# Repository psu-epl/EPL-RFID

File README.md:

# EPL-RFID
RFID system for controlling access to EPL machines

This repo started as copies of two separate Capstone projects in 2018: the CS
backend Capstone called LUCCA (Lab Usage Controller for Centralized Administration)
and the ECE Capstone called EPL RFID Capstone Project.

Here are links to the previous repos:

### LUCCA:
#### Repo: https://github.com/LUCCA-Capstone/LUCCA
#### Wiki: https://github.com/LUCCA-Capstone/LUCCA/wiki

### EPL RFID:
#### Repo: https://github.com/Crimson89/RFID-Capstone
#### Wiki: https://github.com/Crimson89/RFID-Capstone/wiki

# Building ESP-IDF toolchain and environment
From a linux console type the following commands:   

git clone https://github.com/psu-epl/EPL-RFID.git  
cd EPL-RFID  
git submodule update --init  

Then follow "the Setting Up ESP-IDF" directions here: https://github.com/espressif/esp-idf  

This involves lots of building packages from source. You likely don't want to do this very many times.

make sure you edit your PATH variable in your ~/.bashrc to something similar to:

export IDF_PATH=~/path/to/submodule/esp-idf  
export PATH=$PATH:/home/chad/path/to/binaries/xtensa-esp32-elf/bin:/home/chad/path/to/binaries/crosstool-NG/builds/xtensa-esp32-elf/bin/

Bad things happen when you are following the wrong path...

Focus your chi using "echo $PATH"

Code to victory brave warrior!

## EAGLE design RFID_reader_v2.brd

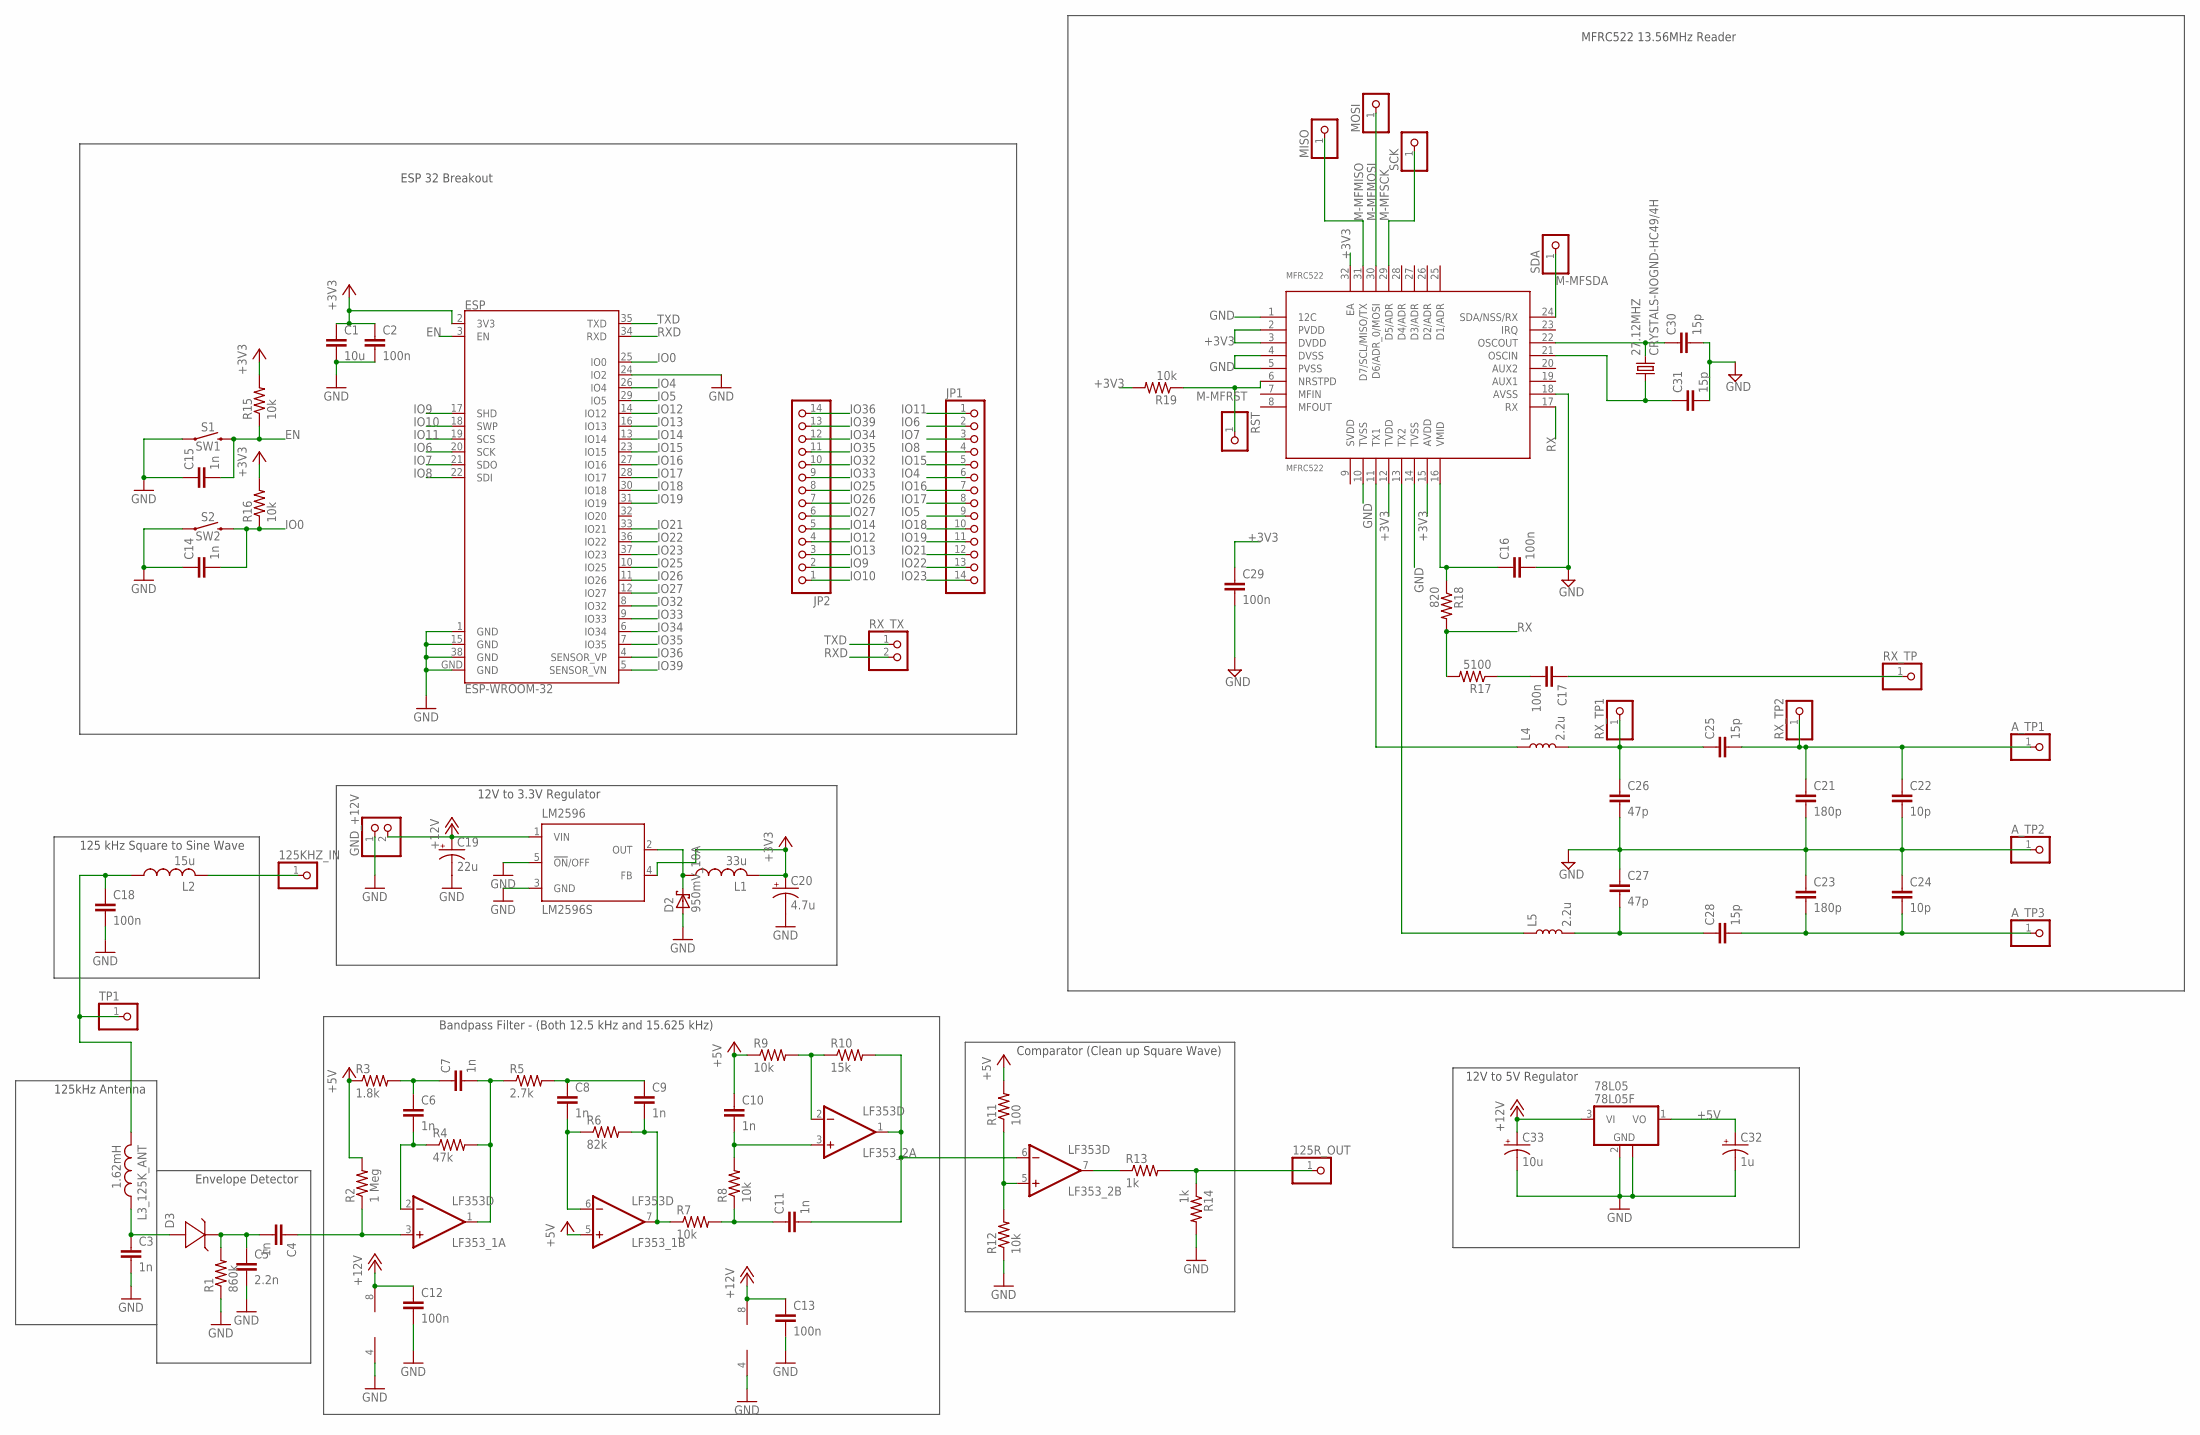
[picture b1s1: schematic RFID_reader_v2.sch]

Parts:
27.12MHZ: CRYSTALS-NOGND-HC49/4H; HC49
78L05: 78L05F; SOT89
125KHZ_IN, 125R_OUT: PINHD-1X1; 1X01
A_TP1, A_TP2, A_TP3: PINHD-1X1; 1X01
C1: 10u; C0805
C2, C12, C13, C18: 100n; C0805
C3, C4, C6, C7, C8, C9, C10, C11, C14, C15: 1n; C0805
C5: 2.2n; C0805
C16, C17, C29: 100n; C0603
C19: 22u; SANYO-OSCON_SMD_B6
C20: 4.7u; SMC_C
C21, C23: 180p; C0603
C22, C24: 10p; C0603
C25, C28, C30, C31: 15p; C0603
C26, C27: 47p; C0603
C32: 1u; SMC_A
C33: 10u; SMC_C
D2: 950mV_10A; SMC
D3: ZENER; SOD123
ESP: ESP-WROOM-32
GND_+12V: PINHD-1X2; 1X02
JP1, JP2: PINHD-1X14; 1X14
L1: 33u; 0207/10
L2: 15u; L2012C
L3_125K_ANT: 1.62mH; 0207/10
L4, L5: 2.2u; 0603
LF353_1, LF353_2: LF353D; SO08
LM2596: LM2596S; TO263-5
MFRC522: MFRC522; MFR522
MISO: PINHD-1X1; 1X01
MOSI: PINHD-1X1; 1X01
R1: 860k; R0805
R2: 1 Meg; R0805
R3: 1.8k; R0805
R4: 47k; R0805
R5: 2.7k; R0805
R6: 82k; R0805
R7, R8, R9, R12, R15, R16: 10k; R0805
R10: 15k; R0805
R11: 100; R0805
R13, R14: 1k; R0805
R17: 5100; R0603
R18: 820; R0603
R19: 10k; R0603
RST: PINHD-1X1; 1X01
RX_TP, RX_TP1, RX_TP2: PINHD-1X1; 1X01
RX_TX: PINHD-1X2; 1X02
S1: SW1; TACTILE_SWITCH_SMD_6.0X3.5MM
S2: SW2; TACTILE_SWITCH_SMD_6.0X3.5MM
SCK: PINHD-1X1; 1X01
SDA: PINHD-1X1; 1X01
TP1: PINHD-1X1; 1X01

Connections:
+3V3: C1.1, C2.1, C20.+, C29.1, ESP.2 (3V3), L1.2, LM2596.4 (FB), MFRC522.2 (PVDD), MFRC522.3 (DVDD), MFRC522.12 (TVDD), MFRC522.15 (AVDD), MFRC522.32 (EA), R15.2, R16.2, R19.2
+5V: 78L05.1 (VO), C10.1, C32.+, LF353_1.5 (+IN), R2.2, R3.1, R9.1, R11.2
+12V: 78L05.3 (VI), C12.1, C13.1, C19.+, C33.+, GND_+12V.2, LF353_1.8 (V+), LF353_2.8 (V+), LM2596.1 (VIN)
EN: C15.2, ESP.3 (EN), R15.1, S1.2
GND: 78L05.2 (GND), 78L05.2@1 (GND), A_TP2.1, C1.2, C2.2, C3.2, C5.2, C12.2, C13.2, C14.1, C15.1, C16.2, C18.2, C19.-, C20.-, C21.2, C22.2, C23.1, C24.1, C26.2, C27.1, C29.2, C30.2, C31.2, C32.-, C33.-, D2.A, ESP.1 (GND), ESP.15 (GND), ESP.24 (IO2), ESP.38 (GND), ESP.GND, GND_+12V.1, LF353_1.4 (V-), LF353_2.4 (V-), LM2596.3 (GND), LM2596.5 (!ON!/OFF), MFRC522.1 (12C), MFRC522.4 (DVSS), MFRC522.5 (PVSS), MFRC522.10 (TVSS), MFRC522.14 (TVSS), MFRC522.18 (AVSS), R1.1, R12.1, R14.2, S1.1, S2.1
IO0: C14.2, ESP.25 (IO0), R16.1, S2.2
IO4: ESP.26 (IO4), JP1.6
IO5: ESP.29 (IO5), JP1.9
IO6: ESP.20 (SCK), JP1.2
IO7: ESP.21 (SDO), JP1.3
IO8: ESP.22 (SDI), JP1.4
IO9: ESP.17 (SHD), JP2.2
IO10: ESP.18 (SWP), JP2.1
IO11: ESP.19 (SCS), JP1.1
IO12: ESP.14 (IO12), JP2.4
IO13: ESP.16 (IO13), JP2.3
IO14: ESP.13 (IO14), JP2.5
IO15: ESP.23 (IO15), JP1.5
IO16: ESP.27 (IO16), JP1.7
IO17: ESP.28 (IO17), JP1.8
IO18: ESP.30 (IO18), JP1.10
IO19: ESP.31 (IO19), JP1.11
IO21: ESP.33 (IO21), JP1.12
IO22: ESP.36 (IO22), JP1.13
IO23: ESP.37 (IO23), JP1.14
IO25: ESP.10 (IO25), JP2.8
IO26: ESP.11 (IO26), JP2.7
IO27: ESP.12 (IO27), JP2.6
IO32: ESP.8 (IO32), JP2.10
IO33: ESP.9 (IO33), JP2.9
IO34: ESP.6 (IO34), JP2.12
IO35: ESP.7 (IO35), JP2.11
IO36: ESP.4 (SENSOR_VP), JP2.14
IO39: ESP.5 (SENSOR_VN), JP2.13
M-MFMISO: MFRC522.31 (D7/SCL/MISO/TX), MISO.1
M-MFMOSI: MFRC522.30 (D6/ADR_0/MOSI), MOSI.1
M-MFRST: MFRC522.6 (NRSTPD), R19.1, RST.1
M-MFSCK: MFRC522.29 (D5/ADR), SCK.1
M-MFSDA: MFRC522.24 (SDA/NSS/RX), SDA.1
unnamed: C4.2, C5.1, D3.C (-), R1.2
unnamed: C4.1, LF353_1.3 (+IN), R2.1
unnamed: D2.C, L1.1, LM2596.2 (OUT)
unnamed: C3.1, D3.A (+), L3_125K_ANT.1
unnamed: 125KHZ_IN.1, L2.2
unnamed: C6.1, C7.1, R3.2
unnamed: C6.2, LF353_1.2 (-IN), R4.1
unnamed: C8.1, C9.1, R5.2
unnamed: C7.2, LF353_1.1 (OUT), R4.2, R5.1
unnamed: C8.2, LF353_1.6 (-IN), R6.1
unnamed: C9.2, LF353_1.7 (OUT), R6.2, R7.1
unnamed: C11.1, R7.2, R8.1
unnamed: C10.2, LF353_2.3 (+IN), R8.2
unnamed: C17.2, R17.1
unnamed: LF353_2.2 (-IN), R9.2, R10.1
unnamed: C11.2, LF353_2.1 (OUT), LF353_2.6 (-IN), R10.2
unnamed: C18.1, L2.1, L3_125K_ANT.2, TP1.1
unnamed: LF353_2.5 (+IN), R11.1, R12.2
unnamed: LF353_2.7 (OUT), R13.1
unnamed: 125R_OUT.1, R13.2, R14.1
unnamed: C27.2, C28.1, L5.2
unnamed: C25.1, C26.1, L4.2, RX_TP1.1
unnamed: C17.1, RX_TP.1
unnamed: A_TP1.1, C21.1, C22.1, C25.2, RX_TP2.1
unnamed: A_TP3.1, C23.2, C24.2, C28.2
OSCIN: 27.12MHZ.1, C31.1, MFRC522.21 (OSCIN)
OSCOUT: 27.12MHZ.2, C30.1, MFRC522.22 (OSCOUT)
RX: MFRC522.17 (RX), R17.2, R18.2
RXD: ESP.34 (RXD), RX_TX.2
TX1: L4.1, MFRC522.11 (TX1)
TX2: L5.1, MFRC522.13 (TX2)
TXD: ESP.35 (TXD), RX_TX.1
VMID: C16.1, MFRC522.16 (VMID), R18.1

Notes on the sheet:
Envelope Detector
Bandpass Filter - (Both 12.5 kHz and 15.625 kHz)
Comparator (Clean up Square Wave)
125kHz Antenna
125 kHz Square to Sine Wave
12V to 5V Regulator
12V to 3.3V Regulator
ESP 32 Breakout
MFRC522 13.56MHz Reader

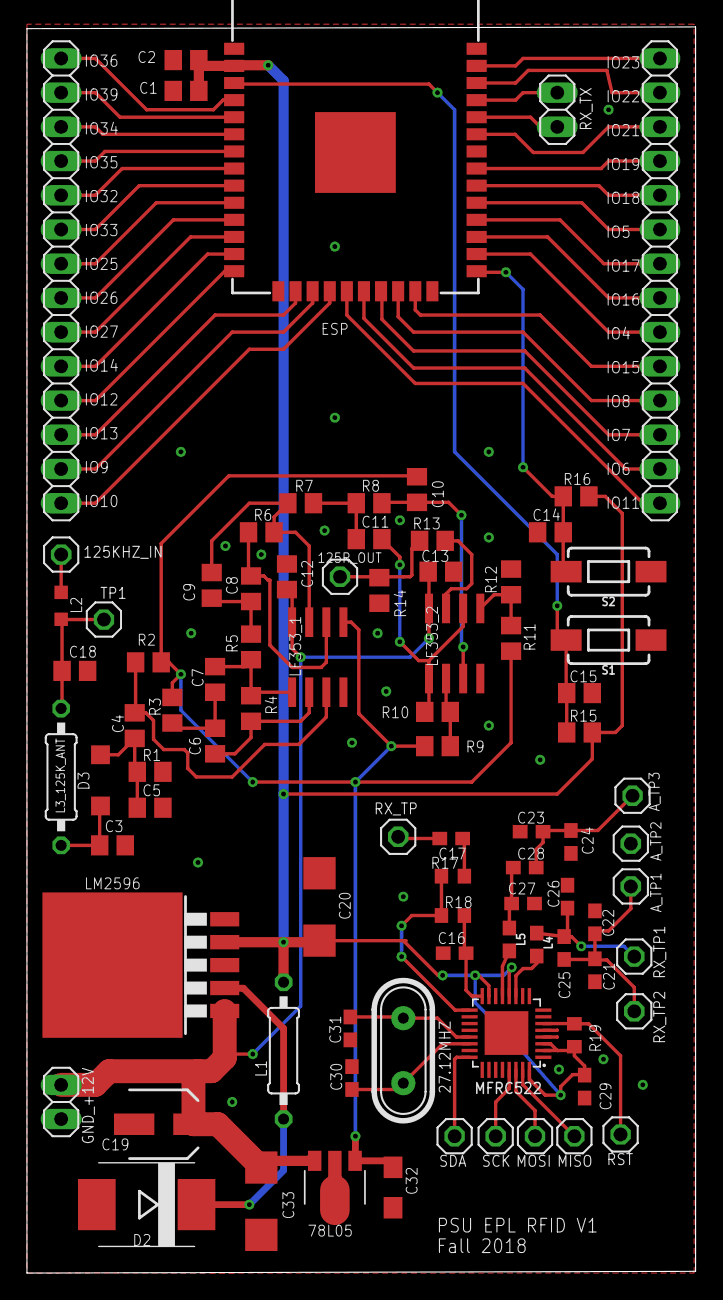
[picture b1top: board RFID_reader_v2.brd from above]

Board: 2 copper layers, 49.6 x 92.5 mm, 86 parts (0 on the bottom side), 72 nets.

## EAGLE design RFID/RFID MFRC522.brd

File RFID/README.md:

# RFID-Capstone
EPL RFID Capstone Project

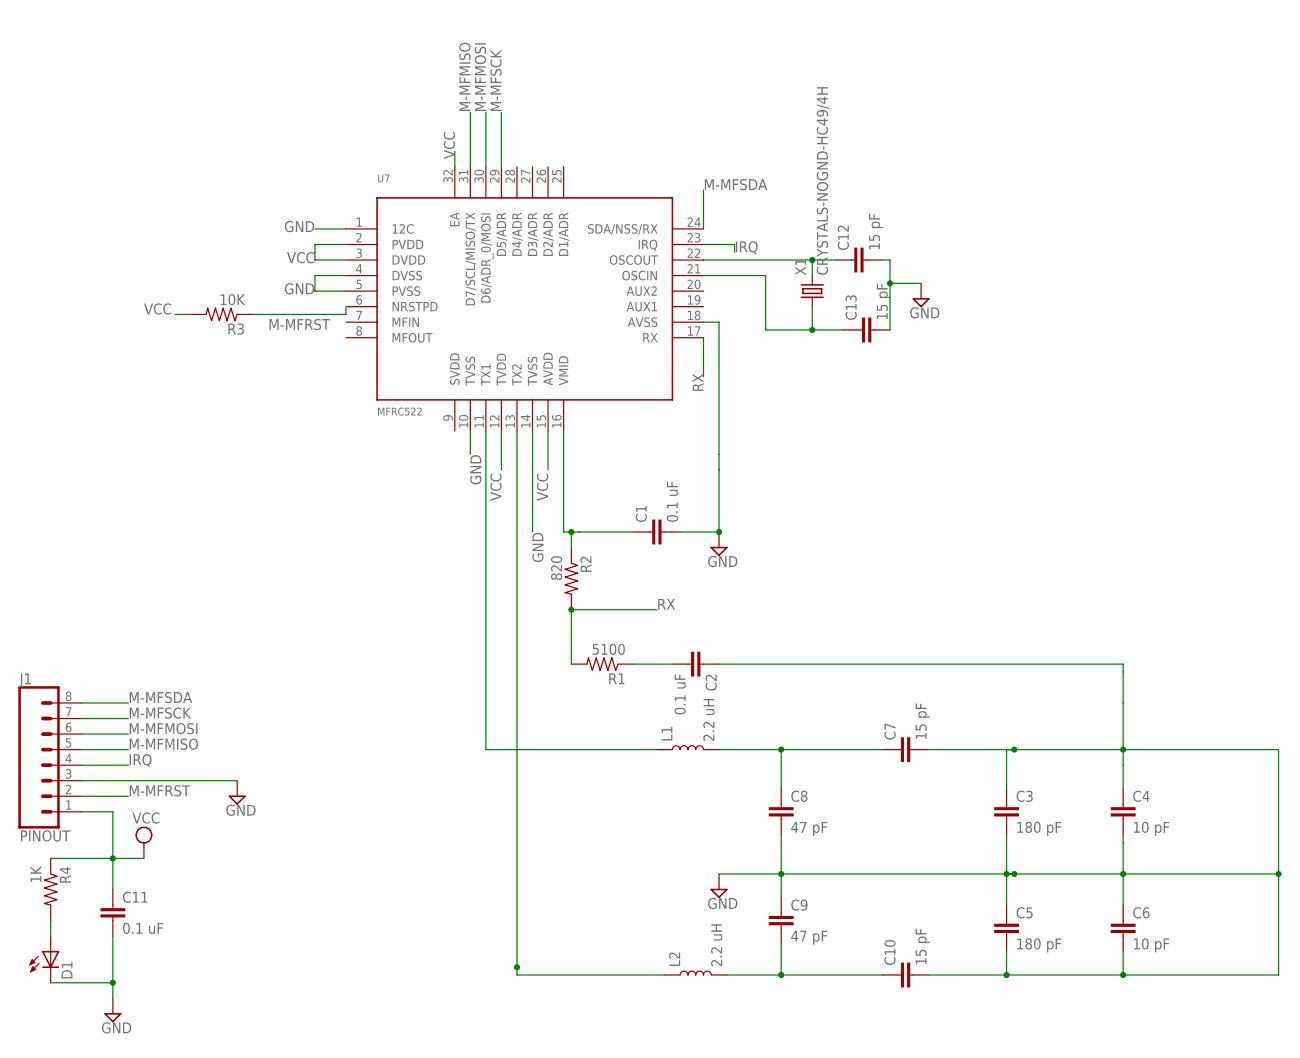
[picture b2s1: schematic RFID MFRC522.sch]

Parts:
C1, C2, C11: 0.1 uF; C0603
C3, C5: 180 pF; C0603
C4, C6: 10 pF; C0603
C7, C10, C12, C13: 15 pF; C0603
C8, C9: 47 pF; C0603
D1: LED; C1210
J1: PINOUT; 1X08_NO_SILK
L1, L2: 2.2 uH; 0603
R1: 5100; R0603
R2: 820; R0603
R3: 10K; R0603
R4: 1K; R0603
U7: MFRC522; MFR522
X1: CRYSTALS-NOGND-HC49/4H; HC49

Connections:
GND: C1.2, C2.1, C3.1, C3.2, C4.1, C4.2, C5.1, C5.2, C6.1, C6.2, C7.2, C8.2, C9.1, C10.2, C11.2, C12.2, C13.2, D1.C, J1.3, U7.1 (12C), U7.4 (DVSS), U7.5 (PVSS), U7.10 (TVSS), U7.14 (TVSS), U7.18 (AVSS)
IRQ: J1.4, U7.23 (IRQ)
M-MFMISO: J1.5, U7.31 (D7/SCL/MISO/TX)
M-MFMOSI: J1.6, U7.30 (D6/ADR_0/MOSI)
M-MFRST: J1.2, R3.1, U7.6 (NRSTPD)
M-MFSCK: J1.7, U7.29 (D5/ADR)
M-MFSDA: J1.8, U7.24 (SDA/NSS/RX)
unnamed: D1.A, R4.2
unnamed: C2.2, R1.1
unnamed: C9.2, C10.1, L2.2
unnamed: C7.1, C8.1, L1.2
OSCIN: C13.1, U7.21 (OSCIN), X1.1
OSCOUT: C12.1, U7.22 (OSCOUT), X1.2
RX: R1.2, R2.2, U7.17 (RX)
TX1: L1.1, U7.11 (TX1)
TX2: L2.1, U7.13 (TX2)
VCC: C11.1, J1.1, R3.2, R4.1, U7.2 (PVDD), U7.3 (DVDD), U7.12 (TVDD), U7.15 (AVDD), U7.32 (EA)
VMID: C1.1, R2.1, U7.16 (VMID)

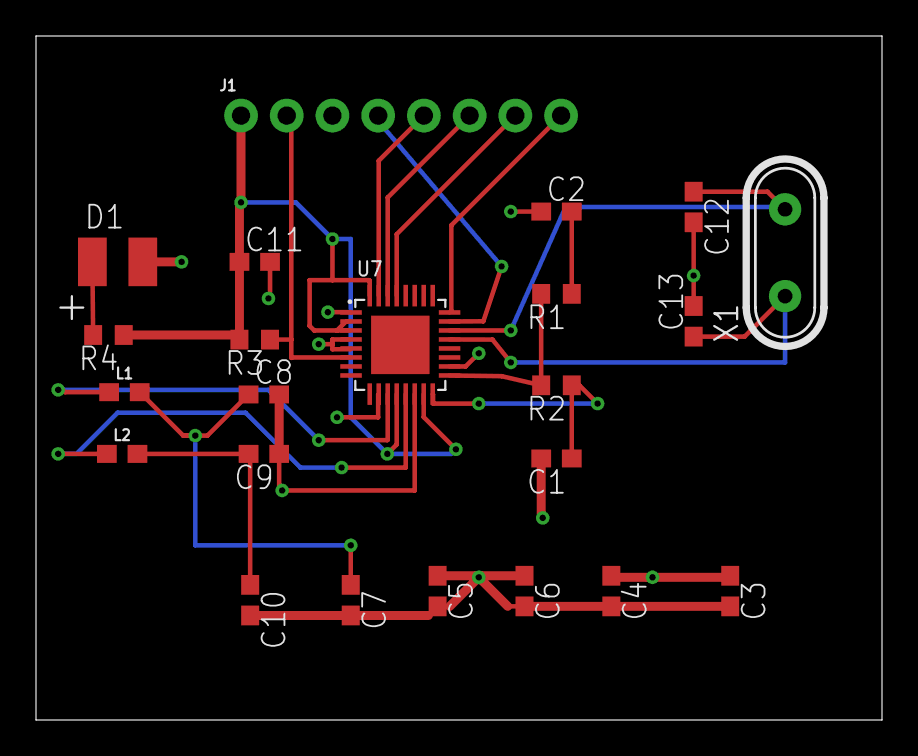
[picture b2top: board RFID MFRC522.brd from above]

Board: 2 copper layers, 47.0 x 38.0 mm, 23 parts (0 on the bottom side), 18 nets.

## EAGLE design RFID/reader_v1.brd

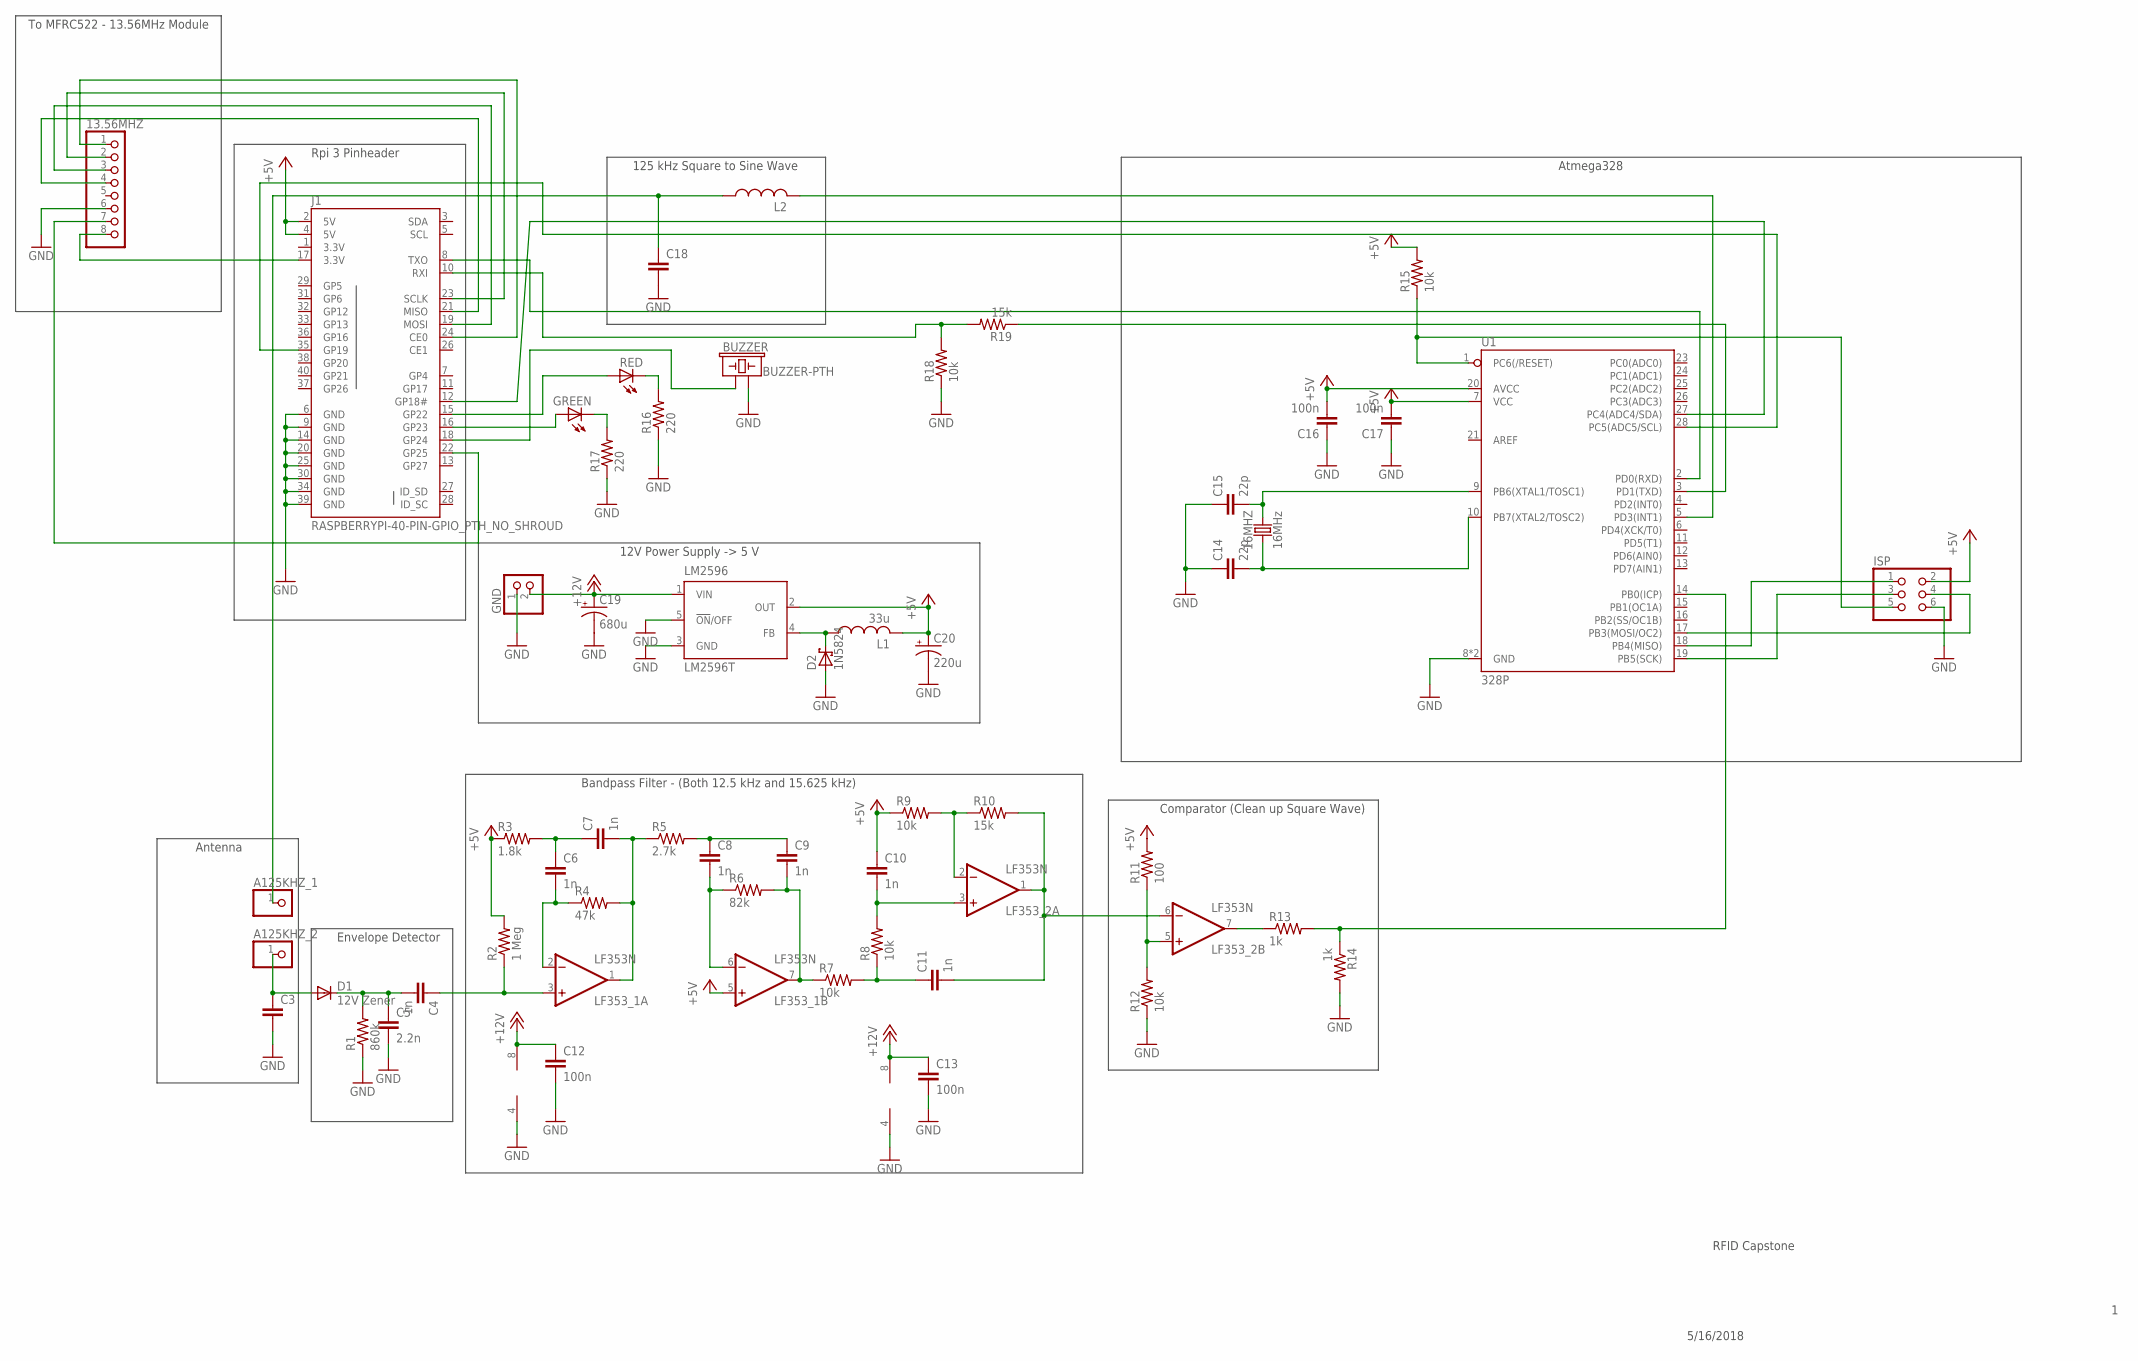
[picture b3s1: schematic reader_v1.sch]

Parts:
13.56MHZ: PINHD-1X8; 1X08
16MHZ: 16MHz; HC49US
A125KHZ_1, A125KHZ_2: PINHD-1X1; 1X01
BUZZER: BUZZER-PTH; BUZZER-12MM
C3, C18: C-EUC0805; C0805
C4, C6, C7, C8, C9, C10, C11: 1n; C0805
C5: 2.2n; C0805
C12, C13, C16, C17: 100n; C0805
C14, C15: 22p; C0805
C19: 680u; E3,5-8
C20: 220u; E2-5
D1: 12V Zener; DO35-7
D2: 1N5824; DO35-7
GND: PINHD-1X2; 1X02
GREEN: LED5MM
ISP: PINHD-2X3; 2X03
J1: RASPBERRYPI-40-PIN-GPIO_PTH_NO_SHROUD; 2X20
L1: 33u; 0207/10
L2: L-US0207/10; 0207/10
LF353_1, LF353_2: LF353N; DIL08
LM2596: LM2596T; T05D
R1: 860k; R0805
R2: 1 Meg; R0805
R3: 1.8k; R0805
R4: 47k; R0805
R5: 2.7k; R0805
R6: 82k; R0805
R7, R8, R9, R12, R15, R18: 10k; R0805
R10, R19: 15k; R0805
R11: 100; R0805
R13, R14: 1k; R0805
R16, R17: 220; R0805
RED: LED5MM
U1: 328P; DIP28

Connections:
3.3V: J1.1 (3.3V)
+5V: C10.1, C16.2, C17.2, C20.+, ISP.2, J1.2 (5V), J1.4 (5V), L1.2, LF353_1.5 (+IN), LM2596.2 (OUT), R2.2, R3.1, R9.1, R11.2, R15.2, U1.7 (VCC), U1.20 (AVCC)
+12V: C12.1, C13.1, C19.+, GND.2, LF353_1.8 (V+), LF353_2.8 (V+), LM2596.1 (VIN)
GND: 13.56MHZ.6, BUZZER.- (2), C3.2, C5.2, C12.2, C13.2, C14.1, C15.1, C16.1, C17.1, C18.2, C19.-, C20.-, D2.A, GND.1, ISP.6, J1.6 (GND), J1.9 (GND), J1.14 (GND), J1.20 (GND), J1.25 (GND), J1.30 (GND), J1.34 (GND), J1.39 (GND), LF353_1.4 (V-), LF353_2.4 (V-), LM2596.3 (GND), LM2596.5 (!ON!/OFF), R1.1, R12.1, R14.2, R16.1, R17.1, R18.1, U1.8 (GND), U1.22 (GND)
unnamed: C4.2, C5.1, D1.C, R1.2
unnamed: C4.1, LF353_1.3 (+IN), R2.1
unnamed: D2.C, L1.1, LM2596.4 (FB)
unnamed: A125KHZ_2.1, C3.1, D1.A
unnamed: ISP.1, U1.18 (PB4(MISO))
unnamed: C6.1, C7.1, R3.2
unnamed: C6.2, LF353_1.2 (-IN), R4.1
unnamed: C8.1, C9.1, R5.2
unnamed: C7.2, LF353_1.1 (OUT), R4.2, R5.1
unnamed: C8.2, LF353_1.6 (-IN), R6.1
unnamed: C9.2, LF353_1.7 (OUT), R6.2, R7.1
unnamed: C11.1, R7.2, R8.1
unnamed: C10.2, LF353_2.3 (+IN), R8.2
unnamed: 16MHZ.1, C14.2, U1.10 (PB7(XTAL2/TOSC2))
unnamed: LF353_2.2 (-IN), R9.2, R10.1
unnamed: C11.2, LF353_2.1 (OUT), LF353_2.6 (-IN), R10.2
unnamed: 16MHZ.2, C15.2, U1.9 (PB6(XTAL1/TOSC1))
unnamed: LF353_2.5 (+IN), R11.1, R12.2
unnamed: LF353_2.7 (OUT), R13.1
unnamed: R13.2, R14.1, U1.14 (PB0(ICP))
unnamed: ISP.5, R15.1, U1.1 (PC6(/RESET))
unnamed: ISP.3, U1.19 (PB5(SCK))
unnamed: ISP.4, U1.17 (PB3(MOSI/OC2))
unnamed: A125KHZ_1.1, C18.1, L2.1
unnamed: 13.56MHZ.8, J1.17 (3.3V)
unnamed: J1.12 (GP18#), U1.27 (PC4(ADC4/SDA))
unnamed: J1.35 (GP19), U1.28 (PC5(ADC5/SCL))
unnamed: L2.2, U1.5 (PD3(INT1))
unnamed: 13.56MHZ.7, J1.22 (GP25)
unnamed: R16.2, RED.K (C)
unnamed: 13.56MHZ.4, J1.21 (MISO)
unnamed: 13.56MHZ.3, J1.19 (MOSI)
unnamed: 13.56MHZ.2, J1.23 (SCLK)
unnamed: 13.56MHZ.1, J1.24 (CE0)
unnamed: GREEN.K (C), R17.2
unnamed: GREEN.A, J1.16 (GP23)
unnamed: J1.15 (GP22), RED.A
unnamed: BUZZER.+ (1), J1.18 (GP24)
unnamed: J1.10 (RXI), R18.2, R19.2
unnamed: R19.1, U1.3 (PD1(TXD))
unnamed: J1.8 (TXO), U1.2 (PD0(RXD))

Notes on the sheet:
RFID Capstone
5/16/2018
12V Power Supply -> 5 V
Envelope Detector
Bandpass Filter - (Both 12.5 kHz and 15.625 kHz)
Comparator (Clean up Square Wave)
Antenna
To MFRC522 - 13.56MHz Module
Atmega328
125 kHz Square to Sine Wave
Rpi 3 Pinheader

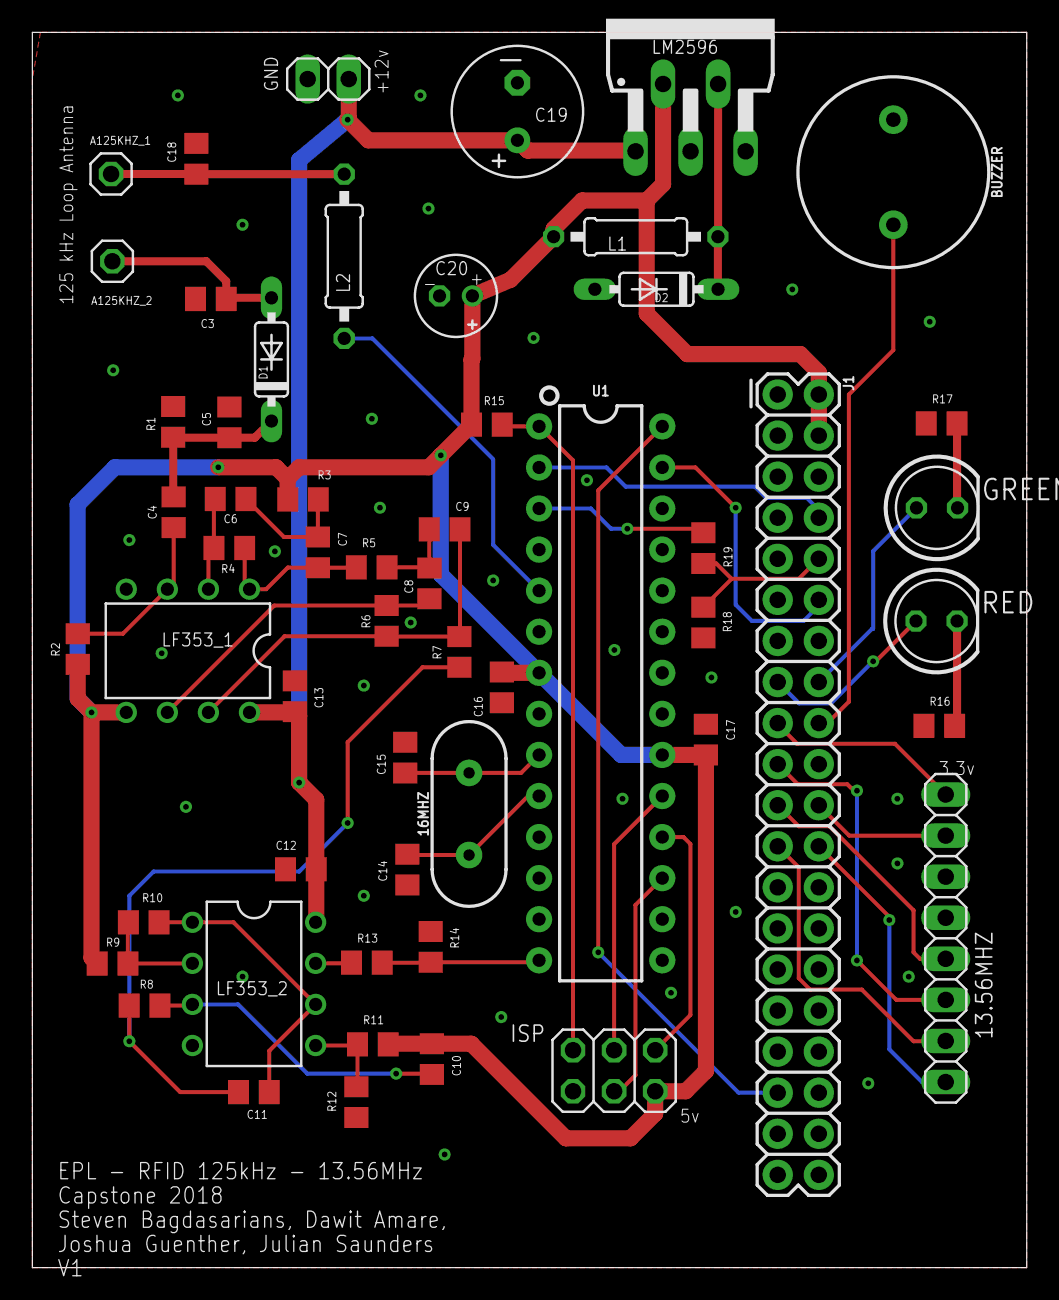
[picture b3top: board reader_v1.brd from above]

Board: 2 copper layers, 61.5 x 76.4 mm, 55 parts (0 on the bottom side), 44 nets.

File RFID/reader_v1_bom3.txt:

Partlist exported from C:/Users/Owner/Documents/eagle/Capstone_RFID/reader_v1.sch at 5/26/2018 2:22 PM

Qty Value                                 Package     Parts                        Description                                                                                                   
1   Red LED                               LED5MM      RED                          LED                                                                     
1   Green LED                             LED5MM      GREEN                        LED                                                                                                                         
1   1 Meg                                 R0805       R2                           RESISTOR, American symbol                                               
1   1.8k                                  R0805       R3                           RESISTOR, American symbol                                               
1   100                                   R0805       R11                          RESISTOR, American symbol                                               
4   100n                                  C0805       C12, C13, C16, C17           CAPACITOR, European symbol                                              
6   10k                                   R0805       R7, R8, R9, R12, R15, R18    RESISTOR, American symbol                                               
1   12V Zener                             Thru Hole   D1                           DIODE                                                                   
2   15k                                   R0805       R10, R19                     RESISTOR, American symbol                                               
1   16MHz                                 CRYSTAL     Y1                           16MHz Crystal                                                           
1   1N5824 (20-40V, 5A Schottkey)         Thru Hole   D2                           Schottky Diode                                                          
2   1k                                    R0805       R13, R14                     RESISTOR, American symbol                                               
7   1n                                    C0805       C4, C6, C7, C8, C9, C10, C11 CAPACITOR, European symbol                                              
1   2.2n                                  C0805       C5                           CAPACITOR, European symbol                                              
1   2.7k                                  R0805       R5                           RESISTOR, American symbol                                               
2   220                                   R0805       R16, R17                     RESISTOR, American symbol                                               
1   220u                                  Polarized   C20                          POLARIZED CAPACITOR, American symbol                                    
2   22p                                   C0805       C14, C15                     CAPACITOR, European symbol                                              
1   328P                                  DIP28       U1                           Atmel 328P                                                              
1   33u                                   Thru Hole   L1                           INDUCTOR, American symbol                                               
1   47k                                   R0805       R4                           RESISTOR, American symbol                                               
1   680u                                  Polarized   C19                          POLARIZED CAPACITOR, American symbol                                    
1   82k                                   R0805       R6                           RESISTOR, American symbol                                               
1   860k                                  R0805       R1                           RESISTOR, American symbol                                               
1   BUZZER (=<3.3V)                       BUZZER-12MM BUZZER                       Buzzer                                                                  
2   LF353N                                DIL08       LF353_1, LF353_2             OP AMP                                                                  
1   LM2596T                               T05D        LM2596                       SIMPLE SWITCHER® Power Converter 150 kHz 3A Step-Down Voltage Regulator 
1   2x20 Female Header		 	  2X20        J1                           Raspberry Pi GPIO Header

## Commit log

2018-07-03 Initial copy from previous repos
    Here are links to the previous repos:
    LUCCA:
    Repo: https://github.com/LUCCA-Capstone/LUCCA
    Wiki: https://github.com/LUCCA-Capstone/LUCCA/wiki
    EPL RFID:
    Repo: https://github.com/Crimson89/RFID-Capstone
2018-08-04 starting work on the esp32. it flashes properly
2018-08-04 switched to branch dev_chad_esp32
2018-08-09 Added esp-idf submodule. Added app_template and app_blinky
2018-08-09 Fixing broken submodule
2018-08-11 Starting app_epl_rfidnode. Connects to a network. Added (but didn't test) pwm and input capture. Needs code cleanup and testing
2018-08-15 added HTTPS request
2018-08-18 pwm ready for initial oscope testing
2018-08-21 holy bugzapper batman, that mosquito was bigger than your face!
2018-08-21 created some certs to test tls
2018-08-23 ready for pwm testing
2018-08-23 authenticating server cert
2018-08-24 testing ledc in the epl
2018-08-27 test setting freq to 120K and 10% duty cycle
2018-08-28 ledc working 125k @ 50% duty cycle. added arduino capture code
2018-08-28 code to test sin wave from the DAC
2018-08-28 working PWM
2018-08-29 Add files via upload
    Rev 1 of attempt to layout MiFare MFRC 522 13.56MHz reader
2018-08-30 copy pasted working code into this. needs cleanup and testing.
2018-09-04 incorrect period time
2018-09-04 now I can talk to the API
2018-09-05 SPI subsystem working
    I was able to use the SPI subsystem to control MAX7219 chip. Now I just need the reader to write the code for it.
2018-09-05 working on hardware timer
2018-09-11 Card Reader initial code
2018-09-12 some more functions to control RC522
2018-09-14 Able to talk SPI between ESP and PCD
2018-09-16 can detect a card now
2018-09-16 fixed bug and improved communication between card and reader
2018-09-29 random things
2018-10-02 hw timer ready for initial testing
2018-10-03 hardware timer is working but something is fucked with the conversion equation or more likely the rtc_clk_apb_freq_get() call
2018-10-03 Changed the timer clock divider so that we get 1us ticks on the timer
2018-10-05 timer is working properly but there is a conversion error. results seem to be in nanoseconds but they should be microseconds
2018-10-05 fixed unit conversion
2018-10-07 some progress on card reading(my own lib)
2018-10-07 trying to use the library now. still having issues
2018-10-07 forgot this file
2018-10-07 Confirm correct PWM frequency, period, and duty cycle using an oscilloscope
2018-10-07 Test timer reload
2018-10-08 Seperate timer_reset and app_good_capture_timer_pwm from app_epl_rfidnode and remove app_epl_rfidnode
2018-10-13 Fix off by 1 bug in the input capture isr
2018-10-13 rethink the algorithm
2018-10-14 Test longer running timer and math
2018-10-20 cleared some warnings
2018-10-20 some progress towards getting the id
2018-10-20 Ready for elp testing
2018-11-13 moved v2 board to RFID
2018-12-08 Changes to get the rest of the ID
2018-12-09 Create program for analyzing 125khz reader
2018-12-09 EPLurbus unem
2018-12-10 Input data from file to buffer as uint
2018-12-11 Combine uint32_t values from data into array of uint64_t values
2018-12-12 Working on bit manipulation
2018-12-12 Working 27bit extraction
2018-12-12 broken
2018-12-13 Templatized important functions
2018-12-13 off to work:(
2018-12-14 Shifting is almost working, find the bug damnit!
2018-12-14 WTF switching to bitsets
2018-12-14 kEPLer > EPLurbus, i hope...
2018-12-15 Make shiftAll work properly
2018-12-15 it's broken but i don't want to lose it
2018-12-15 Working bit pattern initialization
2018-12-15 Hey Chris! This is the bit analyzing branch
2018-12-20 Change ifstream implimentation to std::list
2018-12-22 Heading to Utah
2019-02-03 Bit shifting is fucked
2019-02-04 Need to fix the weird shiftbyone bug
2019-02-06 kEPLer lives!

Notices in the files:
parts and their libraries:
SparkFun-Coils: Licensing: Creative Commons ShareAlike 4.0 International - https://creativecommons.org/licenses/by-sa/4.0
